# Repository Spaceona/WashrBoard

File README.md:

# Washr Board V5.3

The Washr Board is the small circuit board SpaceOna sticks onto a washing machine or dryer. It
feels the machine vibrating, decides whether the machine is running, and reports that over Wi-Fi
so students can see which machines are free.

This README is written for someone with **no electronics background**. It explains what every part
on the board does, how the parts work together, and how to get boards manufactured and assembled.

| Top | Bottom |
| --- | --- |
|  |  |

- Board size: 70.2 mm × 50.2 mm, 2 copper layers, 1.6 mm thick, 4 × M3 mounting holes
- Designed in KiCad by Robbie Leslie. The schematic is in [`docs/WashrBoard-schematic.pdf`](docs/WashrBoard-schematic.pdf)
- Everything you need to order it is in [`fab/`](fab/)

---

## Contents

1. [The 30-second version](#1-the-30-second-version)
2. [Where the board fits in the SpaceOna system](#2-where-the-board-fits-in-the-spaceona-system)
3. [Electronics crash course](#3-electronics-crash-course)
4. [How the board works, block by block](#4-how-the-board-works-block-by-block)
5. [What happens when you plug it in](#5-what-happens-when-you-plug-it-in)
6. [Parts list: what to buy and what each part does](#6-parts-list-what-to-buy-and-what-each-part-does)
7. [Cost estimate](#7-cost-estimate)
8. [Ordering from JLCPCB, step by step](#8-ordering-from-jlcpcb-step-by-step)
9. [When the boards arrive: bring-up checklist](#9-when-the-boards-arrive-bring-up-checklist)
10. [Known quirks and ideas for the next revision](#10-known-quirks-and-ideas-for-the-next-revision)
11. [Glossary](#11-glossary)
12. [Files in this repo](#12-files-in-this-repo)

---

## 1. The 30-second version

```mermaid
flowchart LR
    USB["USB-C (J2)<br/>or JST GH (J5)<br/>5 V in"] --> REG["Regulator U1<br/>5 V → 3.3 V"]
    USB -. "USB data (D+ / D−)" .-> ESD["ESD protection U2"]
    ESD -.-> MCU
    REG --> MCU["ESP32-C3 module U4<br/>the brain + Wi-Fi"]
    REG --> IMU["Motion sensor MT1<br/>ICM-42670-P"]
    IMU -- "I²C (SDA / SCL)" --> MCU
    MCU --> LEDS["Green LED D1<br/>Red LED D2"]
    BTN["BOOT button U3"] --> MCU
    MCU -. "Wi-Fi via external antenna" .-> CLOUD["SpaceOna backend"]
```

1. **Power comes in** as 5 V, from a USB-C cable or a small locking JST connector.
2. **A regulator turns 5 V into 3.3 V**, because the chips on the board run on 3.3 V and would be
   damaged by 5 V.
3. **A motion sensor (IMU)** measures acceleration about 10 times a second.
4. **The ESP32-C3** (a tiny computer with Wi-Fi) reads the sensor. If the readings keep changing,
   the machine is shaking, so it must be running.
5. **The ESP32 sends "in use" or "free" over Wi-Fi** to the SpaceOna server. The website then shows it.
6. **Two LEDs** blink so you can see what the board is doing. **A button** is used when loading new
   software onto it.

That's the whole board. Everything else on it (resistors, capacitors) helps those main parts work
reliably.

---

## 2. Where the board fits in the SpaceOna system

| Piece | Repo | What it does |
| --- | --- | --- |
| **This board (hardware)** | [Spaceona/WashrBoard](https://github.com/Spaceona/WashrBoard) | Senses vibration, talks Wi-Fi |
| Firmware (the code running on the board) | [Spaceona/Washr](https://github.com/Spaceona/Washr) | Detection algorithm, Wi-Fi, server communication. Build with the PlatformIO `custom-board` environment |
| Backend (server) | [Spaceona/backend-go](https://github.com/Spaceona/backend-go) | Stores machine status, authenticates boards, serves firmware updates |
| Website | [Spaceona/washr-frontend-react](https://github.com/Spaceona/washr-frontend-react) | Shows students which machines are free |

The hardware only has to do three things well: stay powered, sense vibration, and connect to Wi-Fi.
All of the "is the machine running?" logic lives in the firmware.

---

## 3. Electronics crash course

You only need a handful of ideas to read this board.

**Voltage, current, ground.** Think of water in pipes. *Voltage* (volts, V) is the pressure,
*current* (amps, A, or milliamps, mA) is how much water flows, and *ground* (GND) is the drain
everything returns to. It is the 0 V reference point. Every circuit is a loop: current leaves the
supply, goes through a part, and returns through GND.

**Power = voltage × current.** Whatever power a part "wastes" turns into heat.

**Resistor (R).** A part that limits how much current can flow. Its value is in ohms (Ω); "10k" means
10,000 Ω. On this board resistors do two jobs: they limit LED current, and they act as **pull-ups**
(explained below).

**Capacitor (C).** A tiny rechargeable reservoir of charge. Chips draw current in sudden gulps (the
Wi-Fi radio especially). A capacitor placed right next to a chip supplies those gulps instantly, so
the voltage doesn't dip. This is called **decoupling**. Values are in farads: µF (microfarads) and
nF (nanofarads).

**LED (D).** A light that only lets current through in one direction. It needs a resistor in series,
or it will draw too much current and burn out.

**IC / chip (U).** A packaged circuit that does something complex: regulate power, run code, sense motion.

**Digital signals.** A chip pin is either **HIGH** (≈3.3 V, logic 1) or **LOW** (≈0 V, logic 0).
A **GPIO** ("general-purpose input/output") is a pin the software can read or drive.

**Pull-up resistor.** A resistor from a pin to 3.3 V. It makes the pin read HIGH by default, but
anything that connects the pin to GND (like a button) easily wins and makes it LOW. Without one, an
unconnected pin "floats" and reads random values.

**I²C.** A way for two chips to talk using just two wires: **SCL** (clock, the "tick" that sets the
pace) and **SDA** (data). Each chip on the bus has an address. This board's IMU uses address `0x68`.
I²C lines need pull-up resistors to work.

**USB data.** USB carries data on two wires, **D+** and **D−**. They always work as a pair.

**Reference designators.** Each part has a letter plus a number printed next to it: **R** resistor,
**C** capacitor, **D** diode/LED, **U** chip, **J** connector or test pad, **H** mounting hole.
**MT1** is the motion sensor, a naming choice from its custom footprint.

---

## 4. How the board works, block by block

The schematic is split into labelled boxes. Each one is explained below, in the order electricity
flows through the board.

### 4.1 USB-C port (J2, R1, R2)

USB-C is where power (and optionally data) comes in.

- **VBUS** is the 5 V power wire from the cable.
- **R1 and R2 (5.1 kΩ) on the CC1 and CC2 pins.** A USB-C charger won't turn its 5 V on until it
  "sees" a device. These two resistors to GND are how the board says "I'm a device, please send
  5 V". There are two because a USB-C plug can go in either way up. **Without them, a USB-C to
  USB-C cable would give the board 0 V.**
- **D+ and D−** are wired to both rows of the connector (A6/B6 and A7/B7), again so the plug works
  either way up. They go through the ESD protector (U2) to the ESP32.
- SBU1/SBU2 (for alternate modes like video) are unused.

### 4.2 JST power connector (J5)

A small 2-pin connector that **latches** so it can't vibrate loose. That matters when you're mounted
on a washing machine. It only carries **5 V and GND, no data**.

> ⚠️ **Only plug in one power source at a time** (it's printed on the board). USB-C and the JST
> connector are wired straight together on the same 5 V line. If both are connected, the two
> supplies push current into each other.
>
> ⚠️ **5 V only.** The regulator can take at most 5.5 V. Feeding the JST 9 V or 12 V will destroy it.

### 4.3 USB protection (U2, USBLC6-2SC6)

When you touch a USB connector you can zap it with thousands of volts of static electricity (ESD).
U2 sits in the D+/D− lines. It does nothing during normal operation, and during a static spike it
dumps the spike into GND before it reaches the ESP32. D+/D− pass straight through U2 (pins 1↔6 and 3↔4).

### 4.4 5 V → 3.3 V regulator (U1, C1, C2)

The ESP32 and the IMU run on 3.3 V. U1 (**TLV1117LV33**) is a *linear regulator* (an "LDO"). It takes
the 5 V in and holds its output at a steady 3.3 V, burning off the difference as a little heat.

- **C1 (1 µF)** on the input and **C2 (1 µF)** on the output keep the regulator stable. Its datasheet
  requires them.
- U1 can supply up to 1 A. The ESP32 draws tens of mA on average, with short peaks of about
  350 mA while it transmits Wi-Fi. That leaves plenty of margin.
- Heat: even at a pessimistic 0.1 A average, (5 V − 3.3 V) × 0.1 A ≈ 0.17 W. The big metal tab on the SOT-223 package spreads
  that into the board.

### 4.5 The brain: ESP32-C3-WROOM-02U (U4)

The big metal-shielded rectangle is a **module**: a complete little computer already built and
certified. Inside the shield there is an ESP32-C3 chip (160 MHz RISC-V processor, 400 KB RAM),
4 MB of flash memory (the "N4" in the name) that stores the firmware, a crystal (the clock), and
the Wi-Fi/Bluetooth radio. Using a module is why this board needs so few extra parts.

**"02U" means the module has no built-in antenna.** It has a tiny **U.FL (IPEX) connector** instead,
the gold circle in the corner of the module. **You must plug an external 2.4 GHz antenna into it**
(see the parts list). Without one, Wi-Fi range is only a few centimetres. The external antenna
also lets the antenna sit outside a metal washing-machine panel, which a built-in antenna couldn't.

The ESP32-C3 has **USB built in** (on GPIO18/19). That means the same USB-C cable powers the
board, uploads new firmware, and shows `Serial.print` output. No separate USB-to-serial chip is needed.

**Pin map**, meaning which ESP32 pin connects to what:

| ESP32-C3 pin | Connected to | Why |
| --- | --- | --- |
| 3V3 | +3.3 V | Power |
| GND | Ground | Power return |
| EN | R8 (10 k) pull-up to 3.3 V, C6 (1 µF) | "Enable". HIGH = run, LOW = held in reset |
| GPIO2 | R9 (10 k) pull-up | Strapping pin, must be HIGH at boot (see below) |
| GPIO4 | IMU **SDA**, R5 (4.7 k) pull-up | I²C data |
| GPIO5 | IMU **SCL**, R3 (4.7 k) pull-up | I²C clock |
| GPIO6 | R4 (75 Ω) → **green LED D1** | `led_1` in firmware |
| GPIO8 | R10 (10 k) pull-up | Strapping pin, must be HIGH to load firmware |
| GPIO9 | R7 (10 k) pull-up, **BOOT button U3**, pad J7 | Strapping pin. LOW at boot = "download mode" |
| GPIO10 | R6 (75 Ω) → **red LED D2** | `led_2` in firmware |
| GPIO18 | USB D− (through U2) | Native USB |
| GPIO19 | USB D+ (through U2) | Native USB |
| GPIO0, 1, 3, 7, 20 (RX), 21 (TX) | Not connected | Spare |

**Strapping pins, explained.** At the instant the ESP32 powers up, it glances at a few pins
(GPIO2, 8 and 9) to decide *how* to start:

- GPIO9 **HIGH** (default, thanks to R7) → run the firmware already stored in flash (normal).
- GPIO9 **LOW** (you're holding the BOOT button) → start the built-in bootloader and wait for new
  firmware over USB ("download mode").
- GPIO8 must be HIGH for download mode to work, and GPIO2 should be HIGH too. R10 and R9 guarantee that.

**EN / reset (R8, C6).** EN must be HIGH for the chip to run. R8 pulls it HIGH. See
[known quirks](#10-known-quirks-and-ideas-for-the-next-revision) for a note about C6.

### 4.6 Motion sensor / IMU (MT1, ICM-42670-P, C3, C4, C5)

An **IMU** ("inertial measurement unit") contains a 3-axis **accelerometer**, which measures
acceleration, including gravity and vibration, and a 3-axis **gyroscope**, which measures rotation.
When a washing machine spins, the accelerometer readings jitter. That jitter is what the firmware
looks for.

How it's wired:

- **VDD and VDDIO → 3.3 V.** VDD powers the sensor and VDDIO sets the voltage its signal pins use.
- **AP_CS → 3.3 V.** Tying this pin HIGH tells the chip "talk I²C, not SPI".
- **AP_AD0 → GND.** This sets the I²C address to `0x68`, which matches `ICM42670 imu(Wire, 0)` in the firmware.
- **SCL/SDA → ESP32 GPIO5/GPIO4**, with **R3 and R5 (4.7 kΩ) pull-ups**, as I²C requires.
- **FSYNC → GND.** This is an unused camera-sync feature, and the datasheet says to ground it.
- **INT1/INT2 not connected.** The firmware *asks* the sensor for data every 100 ms ("polling")
  instead of having the sensor interrupt it.
- **C3 (100 nF), C4 (10 nF), C5 (2.2 µF)** are decoupling capacitors placed right next to the
  sensor. They keep its supply clean so the measurements aren't noisy.

The sensor is a tiny 2.5 × 3 mm LGA package with no legs, just pads underneath. It can't be
hand-soldered easily, which is one reason to get the boards machine-assembled.

### 4.7 LEDs (D1, D2, R4, R6)

- **D1 green**, driven by GPIO6 through R4 (75 Ω)
- **D2 red**, driven by GPIO10 through R6 (75 Ω)

The resistors set the LED current. For the green LED that's (3.3 V − 2.2 V LED drop) ÷ 75 Ω ≈ 15 mA,
bright but safe.

What the current firmware does with them:

| LED | Pattern | Meaning |
| --- | --- | --- |
| Green | Two slow blinks (0.5 s) | Finished an onboarding / setup attempt |
| Green | Very short flash | Logged in to the server (authenticated) |
| Green | Short flash | Status successfully sent to the server |
| Red | Short flash | Board successfully onboarded (registered) with the server |

A brand-new board with no firmware shows **no LEDs at all**. That's normal.

### 4.8 BOOT button (U3) and programming pads (J6–J10)

**U3** is the "P9 button". It connects GPIO9 to GND when pressed. Hold it while plugging in USB to
force download mode. You only need it if the board stops showing up as a USB device, for example
after firmware that crashes immediately.

On the **bottom** of the board are five round pads for a **pogo-pin programming jig**. A jig is a
fixture with spring pins that press onto the pads, so many boards can be programmed quickly without
plugging in cables:

| Pad | Label | Signal |
| --- | --- | --- |
| J6 | 5V | VBUS |
| J8 | D_P | USB D+ |
| J9 | D_N | USB D− |
| J10 | GND | Ground |
| J7 | PGND | GPIO9, reached through the button's internal contact |

The jig shorts **J7 to J10**, which holds GPIO9 LOW, so the board powers up in download mode. The
designer's note in the schematic explains that this pad goes through the button so GPIO9 is never
*permanently* tied to ground.

### 4.9 Test points (J1, J3, J4) and mounting holes (H1–H4)

- The three gold dots labelled **5V / GND / 3.3V** on the top are for a multimeter. They're the
  first thing to check if a board seems dead (see [bring-up](#9-when-the-boards-arrive-bring-up-checklist)).
- **H1–H4** are plated M3 holes for ISO 7380 button-head screws.

### 4.10 The PCB itself

- **2 copper layers** (top and bottom). The copper **traces** are the "wires", and small plated holes
  called **vias** (48 of them) connect the two layers.
- Most of the empty copper area is a **ground fill**: a solid sheet of GND copper. It gives every
  part a short return path and helps with noise.
- The green layer is **solder mask**, which insulates the copper and stops solder from spreading.
  The white text is **silkscreen**.

---

## 5. What happens when you plug it in

1. 5 V arrives. U1 produces 3.3 V. EN goes HIGH, so the ESP32 starts.
2. The ESP32 checks the strapping pins. The button isn't pressed, so it boots the firmware from flash.
3. The firmware starts USB serial, starts I²C on GPIO4/5, and configures the IMU for a ±2 g range.
4. **Every 100 ms** it reads the accelerometer and compares it with the previous reading. If any
   axis changed by at least 0.1 m/s², that counts as "motion seen".
5. **Debouncing.** A counter goes up by 1 when motion is seen and down by 1 when it isn't, and stays
   between 0 and 100. When the counter reaches **30** (≈3 seconds of mostly-shaking), the machine is
   marked **in use**. It goes back to **free** once the counter falls below 30 again. That can take
   up to ~7 s after the machine stops. This filters out one-off bumps like someone closing the lid.
6. **Every 5 s** a second state machine handles the network: load Wi-Fi credentials → connect →
   register with the backend the first time (onboarding) → log in and get a token → send
   `{status, confidence, firmware version}` to the server.
7. The backend can also tell the board to download new firmware over Wi-Fi (an OTA update).

The firmware lives in [Spaceona/Washr](https://github.com/Spaceona/Washr). See that README for
setting up `include/wifi_secrets.h`.

---

## 6. Parts list: what to buy and what each part does

This is exactly what is in [`fab/WashrBoard-BOM-JLCPCB.csv`](fab/WashrBoard-BOM-JLCPCB.csv), the
file you upload to JLCPCB. Stock and prices were checked against JLCPCB's parts library on
**2026-09-29**. **Basic** parts are always loaded on JLCPCB's machines (no extra fee). **Extended**
parts cost a one-time $3.07 loading fee each per order.

| Ref | Qty/board | Part | LCSC # | Library | Unit price | What it does |
| --- | --- | --- | --- | --- | --- | --- |
| U4 | 1 | ESP32-C3-WROOM-02U-N4 | C2926676 | Extended | $3.07 | The brain + Wi-Fi/Bluetooth (needs external antenna) |
| MT1 | 1 | ICM-42670-P IMU | C3288646 | Extended | $2.28 | Senses vibration (accelerometer + gyro) |
| J2 | 1 | GCT USB4105-GF-A USB-C | C3020560 | Extended | $1.30 | Power + USB data in |
| U1 | 1 | TI TLV1117LV33DCYR | C15578 | Extended | $0.26 | 5 V → 3.3 V regulator |
| U2 | 1 | ST USBLC6-2SC6 | C7519 | Extended | $0.18 | Static (ESD) protection for USB data |
| U3 | 1 | C&K PTS526SK15SMTR2LFS | C2689521 | Extended | $0.18 | BOOT button |
| D1 | 1 | Broadcom HSMG-C150 green LED (1206) | C188727 | Extended | $0.20 | Status light |
| D2 | 1 | KENTO KT-0603R red LED (0603) | C2286 | Basic | $0.01 | Status light |
| J5 | 1 | XYECONN XY-SM02B-GHS-TB (JST GH, 2-pin) | C54582897 | Extended | $0.04 | Locking 5 V power input |
| C1, C2, C6 | 3 | 1 µF 50 V X7R (1206) | C1848 | Basic | $0.05 | Regulator stability, EN capacitor |
| C3 | 1 | 100 nF 50 V X7R (1206) | C24497 | Basic | $0.02 | IMU decoupling |
| C4 | 1 | 10 nF 50 V X7R (1206) | C1846 | Basic | $0.02 | IMU decoupling |
| C5 | 1 | 2.2 µF 50 V X7R (1206) | C50254 | Basic | $0.09 | IMU decoupling |
| R1, R2 | 2 | 5.1 kΩ 1% (1206) | C26033 | Extended | $0.01 | Tells USB-C chargers to send 5 V |
| R3, R5 | 2 | 4.7 kΩ 1% (1206) | C17936 | Basic | $0.01 | I²C pull-ups |
| R4, R6 | 2 | 75 Ω 1% (1206) | C17987 | Extended | $0.01 | LED current limit |
| R7–R10 | 4 | 10 kΩ 1% (0805) | C17414 | Basic | $0.004 | Pull-ups on GPIO9, EN, GPIO2, GPIO8 |

**Bought separately (not soldered by the factory):**

| Item | Qty/board | Where | Price | Notes |
| --- | --- | --- | --- | --- |
| 2.4 GHz antenna with U.FL / IPEX-1 (MHF1) plug | 1 | LCSC **C1693673** (HJ-2.4G-IPEX1, 80 mm cable) or any "2.4 GHz U.FL antenna" | ≈ $0.57 | Clicks onto the gold connector on U4. Must be U.FL / IPEX **gen 1 / MHF1**, *not* MHF4 (laptop Wi-Fi cards use MHF4, which won't fit) |
| USB-C cable + 5 V USB power adapter | 1 | Anywhere | — | Any phone charger works |
| M3 button-head screws (ISO 7380) | 4 | Hardware store | — | Mounting |

**Changes from the original BOM** (so the board can actually be ordered today):

- **J5**: the genuine JST SM02B-GHS-TB (C189893) had only **2 in stock**. It's replaced by the
  XYECONN XY-SM02B-GHS-TB, which has the same 1.25 mm GH pitch, the same pad layout (checked against
  the datasheet) and mates with the same GH cables.
- **D2**: the ROHM SML-D12U1WT86 was out of stock and is replaced with the JLCPCB Basic KT-0603R (same 0603 size).
- **Passives** use JLCPCB Basic equivalents wherever one exists in the same size, to avoid extra fees.
  There is no Basic 5.1 k or 75 Ω in 1206, so those two are Extended.
- **Designators**: `R7-R10` became `R7,R8,R9,R10`. JLCPCB can't read ranges and would report the
  parts as missing.

---

## 7. Cost estimate

JLCPCB **Economic PCBA**, fees from [JLCPCB's pricing page](https://jlcpcb.com/help/article/pcb-assembly-price)
(last updated 2026-09-09), part prices checked 2026-09-29.

| Line item | 2 boards | **5 boards** | 10 boards |
| --- | ---: | ---: | ---: |
| Bare PCBs (min. 5; 2-layer, 70 × 50 mm, HASL) | ~$2 | ~$2 | ~$5 |
| Assembly setup fee | $8.18 | $8.18 | $8.18 |
| Stencil | $1.53 | $1.53 | $1.53 |
| Solder joints (128/board × $0.0016) | $0.41 | $1.02 | $2.05 |
| Extended-part loading fee (10 × $3.07) | $30.70 | $30.70 | $30.70 |
| Components (incl. JLCPCB minimum order qty) | ~$34 | ~$50 | ~$77 |
| **Subtotal (before shipping / tax)** | **≈ $77** | **≈ $94** | **≈ $125** |
| Antennas (LCSC, ~$0.57 each) | ~$1 | ~$3 | ~$6 |

On top of that:

- **Shipping:** roughly $15–30 by express courier (DHL/FedEx/UPS), cheaper and slower with
  JLCPCB's economy lines.
- **Import duties / tariffs:** shown at checkout and depend on your country. For US addresses this
  is currently a noticeable extra, so check the number before paying.
- **Budget ≈ $120–150 landed for 5 working boards.**

Why a small order costs this much:

- **The $30.70 of extended-part fees and $9.71 of setup/stencil are charged once per order**, however
  many boards you order. That's why the per-board price drops quickly with quantity.
- Some parts have **minimum order quantities** at JLCPCB. For example, the regulator must be bought
  in 35s (≈ $9) and the USB-C connector in 7s. The leftovers are stored in your JLCPCB account's
  parts inventory for your next order.
- The ESP32 module, IMU and USB-C connector together are ~$6.65 of the ~$7.80 of parts on each board.

**PCBWay** can build the same board, but they quote assembly by hand (about a day) and buy parts
from distributors themselves. For 2–10 boards that usually costs more than JLCPCB. It's a good fallback
if JLCPCB runs out of a part. Upload the same gerbers, the BOM (PCBWay uses the `Manufacturer` + `MPN`
columns) and the CPL file (they call it "centroid").

---

## 8. Ordering from JLCPCB, step by step

You need three files:

| File | What it is | Where |
| --- | --- | --- |
| **Gerber zip** | The PCB drawings the factory uses to make the bare board (one file per copper, mask and silkscreen layer, plus drill files) | Generate from KiCad (below). Gerbers are git-ignored in this repo |
| **BOM** (bill of materials) | Which part goes where | [`fab/WashrBoard-BOM-JLCPCB.csv`](fab/WashrBoard-BOM-JLCPCB.csv) |
| **CPL** (component placement list) | The X/Y position and rotation of every part, for the pick-and-place robot | [`fab/WashrBoard-CPL-JLCPCB.csv`](fab/WashrBoard-CPL-JLCPCB.csv) |

**Making the gerber zip in KiCad** (open `WashrBoard.kicad_pro`, then the PCB editor):

1. *File → Fabrication Outputs → Gerbers*. Tick F.Cu, B.Cu, F.Paste, B.Paste, F.Silkscreen,
   B.Silkscreen, F.Mask, B.Mask and Edge.Cuts. Click **Plot**.
2. In the same window click **Generate Drill Files…**, then **Generate**.
3. Zip all the files it created into one `.zip`.

**On jlcpcb.com:**

1. Click **Order Now / Instant Quote** and upload the gerber zip. It should detect **2 layers,
   70.2 × 50.2 mm**.
2. PCB options: Qty **5**, thickness **1.6 mm**, any colour (green is fastest). Surface finish
   **HASL** is fine. **ENIG** (gold) gives flatter pads, which helps the tiny leadless IMU, but
   costs more. Leave the other options on their defaults.
3. Turn on **PCB Assembly**: type **Economic**, side **Top**, PCBA qty **5** (or 2), tooling holes
   **Added by JLCPCB**. Click **Next**.
4. Upload **BOM** = `WashrBoard-BOM-JLCPCB.csv` and **CPL** = `WashrBoard-CPL-JLCPCB.csv`. If it
   asks you to match columns: Comment → Comment, Designator → Designator, Footprint → Footprint,
   LCSC Part # → JLCPCB Part #.
5. On the parts page, **all 17 lines should be matched and in stock**. If one shows a shortage, click
   it and choose another part with the same value and package (e.g. "1206", "0805").
6. **Check the placement preview carefully.** KiCad and JLCPCB sometimes disagree on rotation. For
   each part, the **pin-1 dot** in the preview should sit on the pin-1 mark of the footprint. Pay
   special attention to **U1, U2, U4, MT1** and the LED polarity of **D1/D2**. Also check that
   **J2 and J5 face off the board edge**. Rotate anything that's wrong in the viewer.
7. **Save to Cart**. Add the antennas on **lcsc.com** (C1693673). JLCPCB and LCSC are sister
   companies, so you can use the same login. Then check out.
8. A JLCPCB engineer reviews every order (DFM review). They may email or post questions on the order
   page, for example about a part rotation or about the connectors hanging over the board edge.
   Answer them promptly or the order waits.

---

## 9. When the boards arrive: bring-up checklist

1. **Look** at each board under good light: no obvious solder blobs bridging pins, and U4, MT1 and
   the LEDs are the right way round.
2. **Short test (unpowered).** Set a multimeter to resistance/continuity. Measure between the
   **5V** and **GND** test points, then between **3.3V** and **GND**. You should *not* see ~0 Ω
   (a beep). A beep means a short, so don't power that board.
3. **Plug in the antenna** (push the U.FL plug straight down until it clicks) *before* running
   Wi-Fi firmware.
4. **Power it over USB-C.** Measure **3.3V → GND**. It should read 3.25–3.35 V. Nothing should get
   hot. A blank board shows no LEDs, which is normal.
5. **Flash the firmware.** Open [Spaceona/Washr](https://github.com/Spaceona/Washr) in PlatformIO,
   select the **`custom-board`** environment, create `include/wifi_secrets.h`, then Upload.
   - If no USB port appears, **hold the BOOT button (U3)**, plug in USB, release, and upload again.
6. **Open the serial monitor** (115200 baud). You should see it connect to Wi-Fi and talk to the
   server, and the green LED should flash on each successful status update.
7. **Shake it.** Tap the board on a table repeatedly for a few seconds. The reported status should
   switch to "in use", then back to "free" a few seconds after you stop.

---

## 10. Known quirks and ideas for the next revision

These don't stop V5.3 from working, but they're worth knowing:

1. **C6 is wired from 3.3 V to EN instead of from EN to GND.** Espressif recommends a 10 kΩ pull-up
   plus a 1 µF capacitor *to ground* on EN. That delays start-up by a few milliseconds until the supply is
   stable. With C6 connected to 3.3 V, the delay doesn't happen: EN rises at the same moment as the
   supply. From a normal USB supply the ESP32's internal power-on reset still handles this. If a
   board ever fails to start on power-up but works after replugging, this is the first suspect.
   The fix for V5.4 is to move C6 pin 1 from +3.3V to GND.
2. **No protection between the USB-C and JST 5 V inputs** (hence "Only use one connector at a
   time"). A Schottky diode or a small "ideal diode" chip on each input would make it safe to plug
   in both.
3. **No reverse-polarity or over-voltage protection on the JST input.** A backwards or 12 V
   cable will damage the board.
4. **The IMU interrupt pins aren't connected**, so the ESP32 must stay awake and poll. That's fine
   on USB power. For a battery version, wiring INT1 to a spare GPIO would allow deep sleep with
   wake-on-motion.
5. **Part availability.** The genuine JST GH connector ran out at JLCPCB (the clone is used above).
   Stock of the regulator (C15578, a few hundred left) and the ESP32 module (C2926676, about 800 left)
   is worth checking before each order.
6. **KiCad version.** The design files are saved in KiCad 8 format. Opening them in KiCad 9/10
   rewrites them in the newer format. Don't commit that upgrade unless the whole team moves to the
   new version.

---

## 11. Glossary

| Term | Meaning |
| --- | --- |
| **BOM** | Bill of materials: the list of parts to buy |
| **CPL / centroid / pick-and-place file** | Position + rotation of each part for the assembly robot |
| **Gerber** | The standard file format that describes each PCB layer |
| **PCB / PCBA** | Printed circuit board / PCB *Assembly* (board with parts soldered on) |
| **SMT / SMD** | Surface-mount technology/device: parts soldered on top of pads, not through holes |
| **Stencil** | Metal sheet used to print solder paste onto the pads before parts are placed |
| **Reflow** | Oven step that melts the solder paste so parts are soldered in place |
| **Footprint** | The copper pad pattern on the PCB for one part |
| **1206 / 0805 / 0603** | Standard sizes for small parts: 1206 = 3.2 × 1.6 mm, 0805 = 2.0 × 1.25 mm, 0603 = 1.6 × 0.8 mm |
| **LCSC part #** | The "C12345" catalogue number JLCPCB uses to identify a part |
| **Basic / Extended part** | JLCPCB parts that are always loaded on the machines (free) / loaded just for you ($3.07 each per order) |
| **LDO** | Low-dropout linear regulator: turns a higher voltage into a lower, steady one |
| **ESD / TVS** | Electrostatic discharge (static shock) / the protection diodes that absorb it |
| **IMU** | Inertial measurement unit: accelerometer + gyroscope |
| **I²C** | Two-wire chip-to-chip bus (SCL clock + SDA data) |
| **GPIO** | General-purpose input/output pin |
| **Pull-up** | Resistor that makes a pin read HIGH unless something pulls it LOW |
| **Decoupling capacitor** | Capacitor next to a chip that keeps its supply voltage steady |
| **Strapping pin** | A pin the ESP32 reads at power-up to decide how to boot |
| **U.FL / IPEX / MHF1** | Tiny snap-on RF connector for the external antenna |
| **OTA** | Over-the-air firmware update via Wi-Fi |
| **DFM** | Design for manufacturing: the factory's check that your board can be built |

---

## 12. Files in this repo

| Path | What it is |
| --- | --- |
| `WashrBoard.kicad_pro` | KiCad project file. Open this one |
| `WashrBoard.kicad_sch` | Schematic (the circuit diagram) |
| `WashrBoard.kicad_pcb` | PCB layout (where parts and traces physically go) |
| `Library/` | Custom symbols, footprints and 3D model for the IMU, the button and the SpaceOna logo |
| `docs/WashrBoard-schematic.pdf` | Schematic as a PDF, readable without KiCad |
| `docs/images/` | 3D renders of the top and bottom of the board |
| `fab/WashrBoard-BOM-JLCPCB.csv` | Upload-ready BOM with LCSC part numbers |
| `fab/WashrBoard-CPL-JLCPCB.csv` | Upload-ready placement file |

Older board revisions are archived in [Spaceona/WashrBoardArchive](https://github.com/Spaceona/WashrBoardArchive).

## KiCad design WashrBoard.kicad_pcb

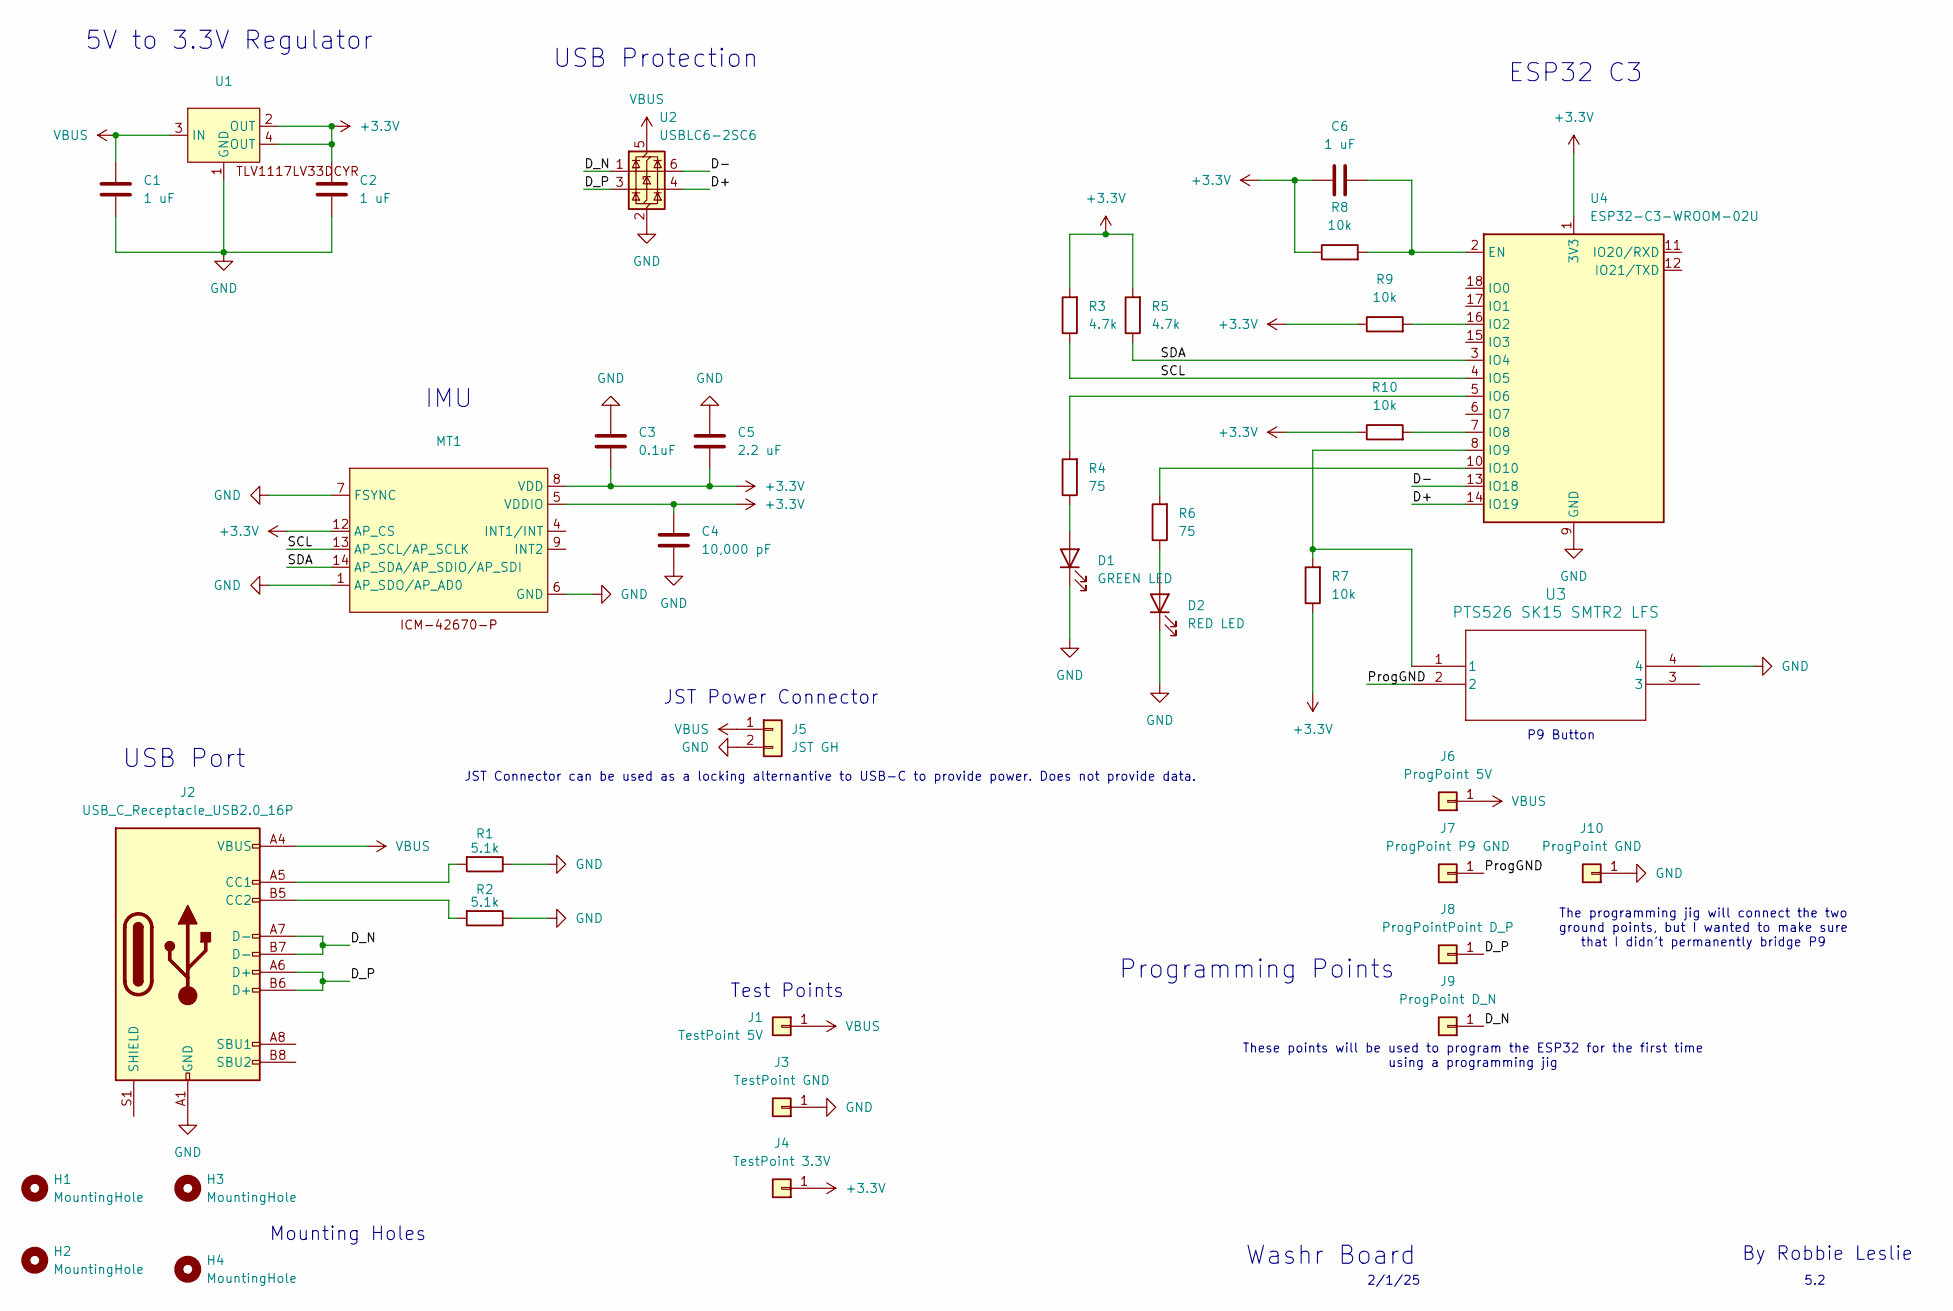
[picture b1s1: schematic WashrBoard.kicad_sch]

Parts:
C1, C2, C6: 1 uF; C_1206_3216Metric; Manufacturer Part Number CL31B105KCHNNNE
C3: 0.1uF; C_1206_3216Metric; Manufacturer Part Number 1206B104K500CT
C4: 10,000 pF; C_1206_3216Metric; Manufacturer Part Number CC1206KRX7R9BB103
C5: 2.2 uF; C_1206_3216Metric; Manufacturer Part Number UMK316BJ225KD-T
D1: GREEN LED; LED_1206_3216Metric; Manufacturer Part Number HSMG-C150
D2: RED LED; LED_0603_1608Metric; Manufacturer Part Number SML-D12U1WT86
H1, H2, H3, H4: MountingHole; MountingHole_3.2mm_M3_ISO7380_Pad
J1: TestPoint 5V; TestPoint_Pad_D1.0mm
J2: USB_C_Receptacle_USB2.0_16P; USB_C_Receptacle_GCT_USB4105-xx-A_16P_TopMnt_Horizontal; Manufacturer Part Number USB4105-GF-A
J3: TestPoint GND; TestPoint_Pad_D1.0mm
J4: TestPoint 3.3V; TestPoint_Pad_D1.0mm
J5: JST GH; JST_GH_SM02B-GHS-TB_1x02-1MP_P1.25mm_Horizontal; Manufacturer Part Number SM02B-GHS-TB
J6: ProgPoint 5V; TestPoint_Pad_D1.0mm
J7: ProgPoint P9 GND; TestPoint_Pad_D1.0mm
J8: ProgPointPoint D_P; TestPoint_Pad_D1.0mm
J9: ProgPoint D_N; TestPoint_Pad_D1.0mm
J10: ProgPoint GND; TestPoint_Pad_D1.0mm
MT1: IMU; XDCR_ICM-42670-P; Manufacturer Part Number ICM-42670-P
R1, R2: 5.1k; R_1206_3216Metric; Manufacturer Part Number CRCW12065K10FKEA
R3, R5: 4.7k; R_1206_3216Metric; Manufacturer Part Number RT1206FRE074K7L
R4, R6: 75; R_1206_3216Metric; Manufacturer Part Number CRCW120675R0FKEA
R7, R8, R9, R10: 10k; R_0805_2012Metric; Manufacturer Part Number RR1220P-103-D
U1: Regulator; SOT-223; Manufacturer Part Number TLV1117LV33DCYR
U2: USBLC6-2SC6; SOT-23-6; Manufacturer Part Number USBLC6-2SC6
U3: PTS526 SK15 SMTR2 LFS; PTS526SK15SMTR2 LFS; Manufacturer Part Number PTS526SK15SMTR2 LFS
U4: ESP32-C3-WROOM-02U; Manufacturer Part Number ESP32-C3-WROOM-02U-N4

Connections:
+3.3V: C2.2, C3.2, C4.1, C5.2, C6.1, J4.1, MT1.5 (VDDIO), MT1.8 (VDD), MT1.12 (AP_CS), R3.2, R5.2, R7.1, R8.1, R9.1, R10.1, U1.2 (OUT), U1.4 (OUT), U4.1 (3V3)
/D+: U2.4 (I/O2), U4.14 (IO19)
/D-: U2.6 (I/O1), U4.13 (IO18)
/D_N: J2.A7 (D-), J2.B7 (D-), J9.1, U2.1 (I/O1)
/D_P: J2.A6 (D+), J2.B6 (D+), J8.1, U2.3 (I/O2)
/ProgGND: J7.1, U3.2
/SCL: MT1.13 (AP_SCL/AP_SCLK), R3.1, U4.4 (IO5)
/SDA: MT1.14 (AP_SDA/AP_SDIO/AP_SDI), R5.1, U4.3 (IO4)
GND: C1.1, C2.1, C3.1, C4.2, C5.1, D1.1 (K), D2.1 (K), J2.A1 (GND), J2.A12 (GND), J2.B1 (GND), J2.B12 (GND), J3.1, J5.2, J10.1, MT1.1 (AP_SDO/AP_AD0), MT1.6 (GND), MT1.7 (FSYNC), R1.1, R2.1, U1.1 (GND), U2.2 (GND), U3.4, U4.9 (GND), U4.19 (GND)
unnamed: D1.2 (A), R4.1
unnamed: D2.2 (A), R6.1
unnamed: J2.A5 (CC1), R1.2
unnamed: J2.B5 (CC2), R2.2
unnamed: C6.2, R8.2, U4.2 (EN)
unnamed: R9.2, U4.16 (IO2)
unnamed: R4.2, U4.5 (IO6)
unnamed: R10.2, U4.7 (IO8)
unnamed: R7.2, U3.1, U4.8 (IO9)
unnamed: R6.2, U4.10 (IO10)
VBUS: C1.2, J1.1, J2.A4 (VBUS), J2.A9 (VBUS), J2.B4 (VBUS), J2.B9 (VBUS), J5.1, J6.1, U1.3 (IN), U2.5 (VBUS)

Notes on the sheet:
IMU
5V to 3.3V Regulator
Test Points
Washr Board
Programming Points
JST Power Connector
2/1/25
JST Connector can be used as a locking alternantive to USB-C to provide power. Does not provide data.
ESP32 C3
USB Port
By Robbie Leslie
USB Protection
The programming jig will connect the two ground points, but I wanted to make sure that I didn't permanently bridge P9
These points will be used to program the ESP32 for the first time using a programming jig
P9 Button
5.2
Mounting Holes

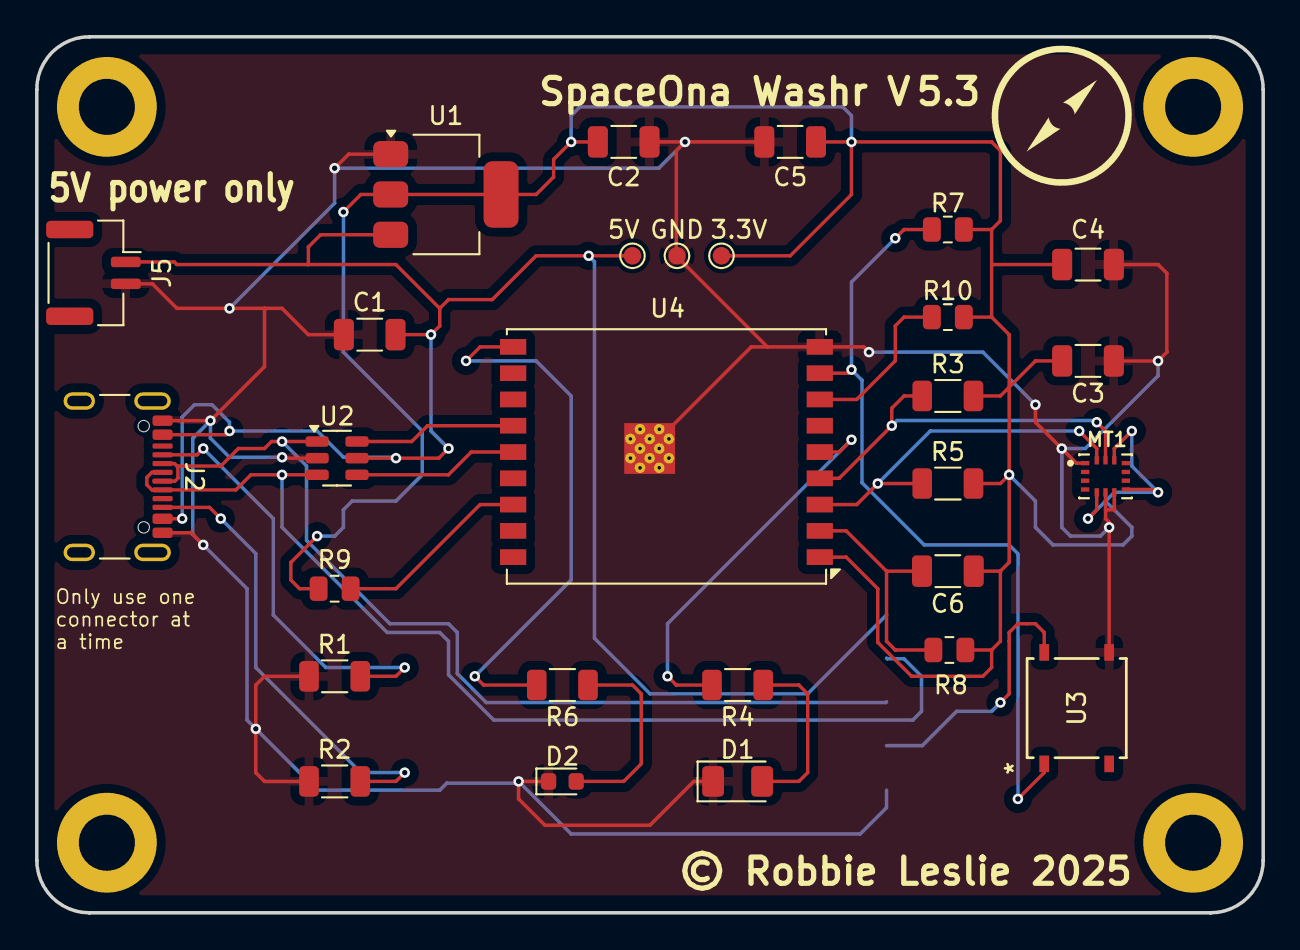
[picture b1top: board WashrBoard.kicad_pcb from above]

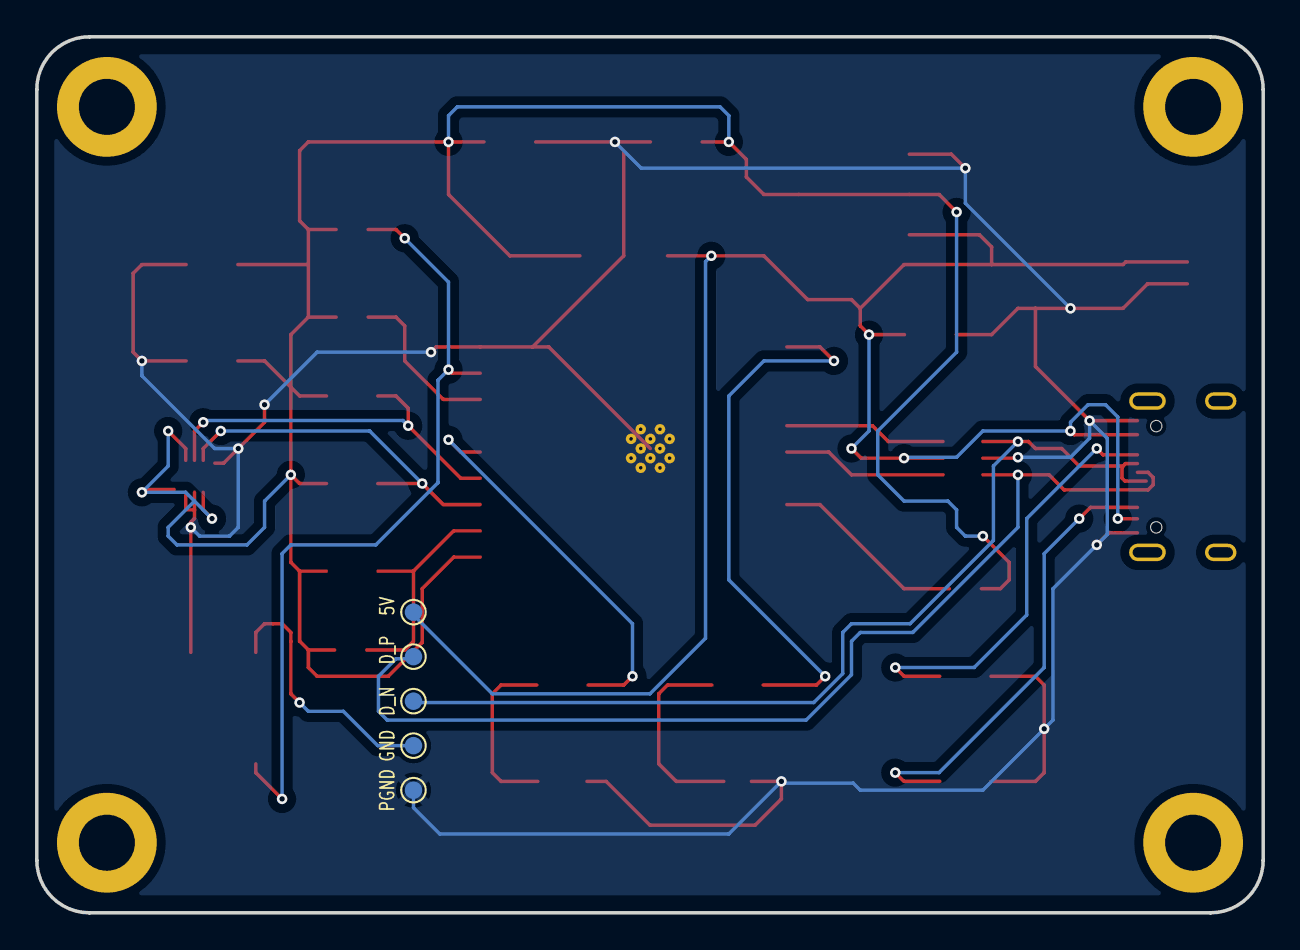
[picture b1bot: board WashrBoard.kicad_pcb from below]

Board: 2 copper layers, 70.0 x 50.0 mm, 37 parts (5 on the bottom side), 20 nets.

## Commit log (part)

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2024-08-09 Finished schematic
2024-08-10 First version of routing
2024-08-10 Added gitignore and removed reports files from git
2024-08-10 Updated connections on PCB
2024-08-10 Swapped USB C connector
2024-08-10 Added branding
2024-08-10 Added ESP32 schematic library
2024-08-10 Renamed schematic and PCB to v1
2024-08-11 Added GND test pads
2024-08-11 Updated BOM
2024-08-11 Added libraries for ESP32 WROOM and Mini boards
2024-08-11 Updated gitignore
2024-08-13 Updated routing a little bit
2024-08-19 Fix 3.3V not being connected
2024-08-19 Fixed USB data lines
2024-08-22 Fixed bugs with first version of design
2024-08-22 Started work on V2 board
2024-08-23 Finished V2 design
2024-08-25 Did first version of programer board
2024-08-27 Swapped out to larger components
2024-08-27 Moved R2
2024-10-02 Switched P9 switch for button, changed red LED to diffused, and removed extra testpoints
2024-10-02 Updated some traces
2025-01-17 Added V4 schematic
2025-01-18 Initial PCB layout w/out traces
2025-01-18 Initial routing
2025-01-18 Finished routing of V4
2025-01-18 Prepared schematic for BOM export
2025-01-18 Adjusted testpoint pad spacing
2025-01-19 Changed label on JST connector
2025-01-19 Updated version, and moved old designs to archive repo
2025-01-19 Updated silkscreen
2025-01-19 Annotated schematic
2025-01-19 Added details to PCB drawing
2025-01-26 Swapped JST XH for GH connector
2025-02-02 Swapped screwholes to ISO 7380
2025-02-02 Added fill zones
2025-02-26 Added solder paste circle to mounting holes so they will be cut in the stencil

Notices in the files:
WashrBoard.kicad_pcb:
© Robbie Leslie 2025
